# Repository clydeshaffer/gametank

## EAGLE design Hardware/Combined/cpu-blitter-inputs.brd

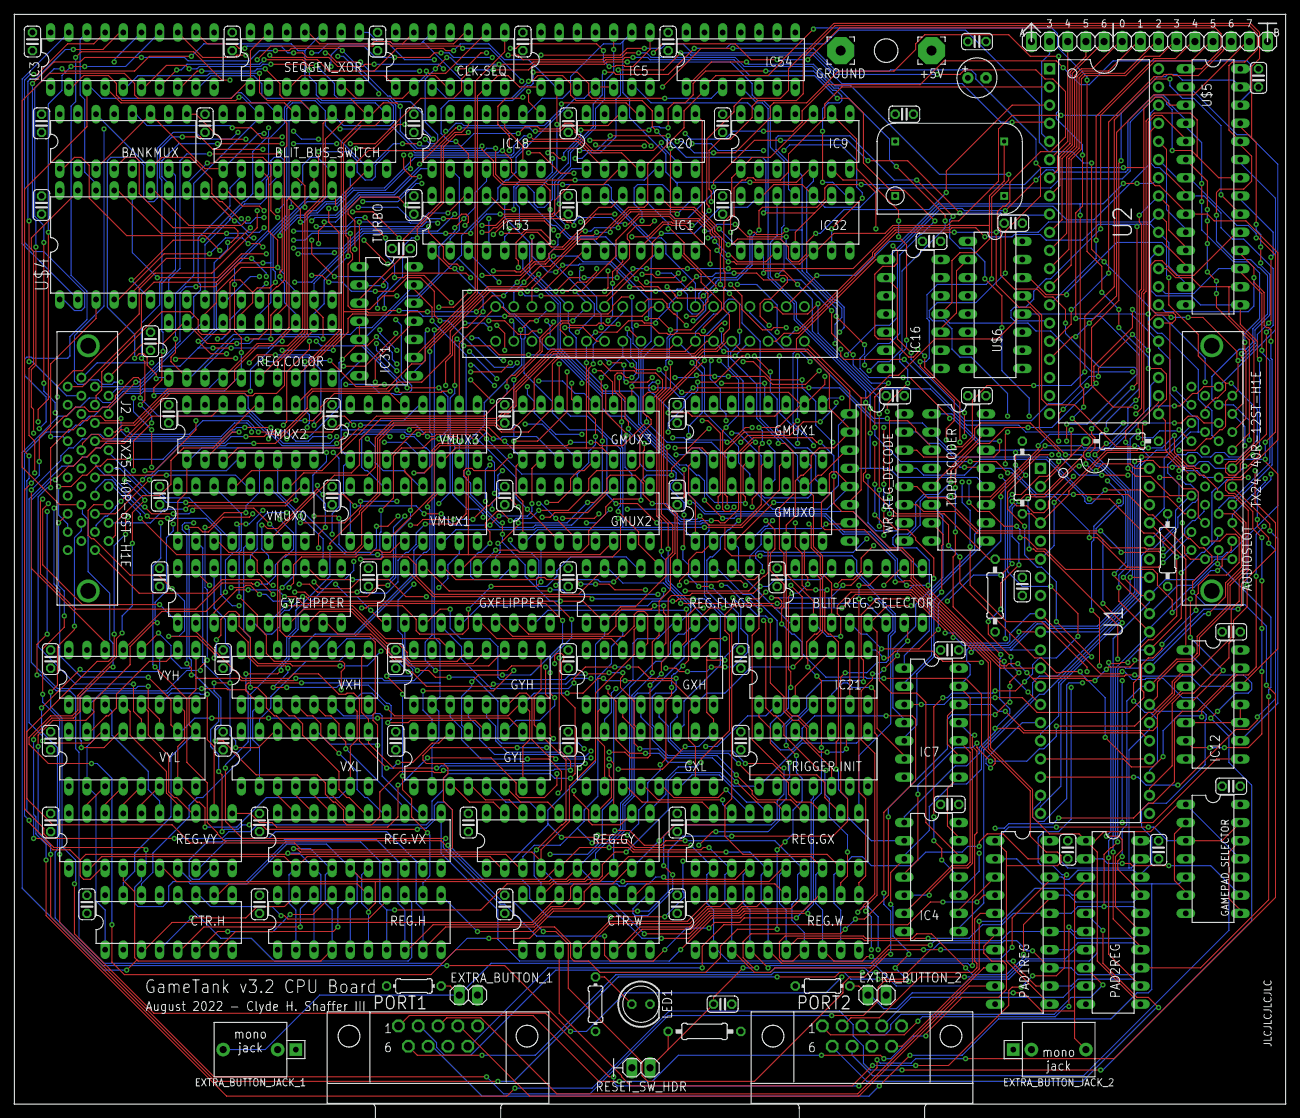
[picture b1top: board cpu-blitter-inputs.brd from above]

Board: 4 copper layers, 177.8 x 152.4 mm, 144 parts (0 on the bottom side), 318 nets.

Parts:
+5V: 3,81/1,4
AUDIOSLOT: TX24-40R-12ST-H1E; CON40_2X20_MU_TX24_JAE
BANKMUX: 74LS257N; DIL16
BLIT_BUS_SWITCH: 74640N; DIL20
BLIT_REG_SELECTOR: 74HC238; DIL16
C1, C2, C3, C4, C5, C6, C7, C8, C9, C10, C11, C12, C13, C14, C15, C16, C17, C18, C19, C20, C21, C22, C23, C24, C25, C26, C27, C28, C29, C30, C31, C32, C33, C34, C35, C36, C38, C39, C40, C41, C42, C43, C44, C45, C46, C57: C025-024X044
C47, C48, C49, C50, C51, C52, C53, C54, C55, C56, C59, C60, C61, C62, C63: 0.1uF; C025-024X044
C58: E2,5-6
CLK.SEQ: 74S08N; DIL14
CTR.H, CTR.W: CD40103; DIL16
EXTRA_BUTTON_1, EXTRA_BUTTON_2: 1X02
EXTRA_BUTTON_JACK_1, EXTRA_BUTTON_JACK_2: MONOJACK
GAMEPAD_SELECTOR: 74LS74N; DIL14
GMUX0, GMUX1, GMUX2, GMUX3: 74LS257N; DIL16
GROUND: 3,81/1,4
GXFLIPPER: 74AHC8541; DIL20
GXH: 74HC163; DIL16
GXL: 74HC163; DIL16
GYFLIPPER: 74AHC8541; DIL20
GYH: 74HC163; DIL16
GYL: 74HC163; DIL16
IC1, IC7, IC12: 74S08N; DIL14
IC3: 74HC573N; DIL20
IC4, IC16, IC53: 7404N; DIL14
IC5, IC21, IC31: 7400N; DIL14
IC9: 74LS74N; DIL14
IC18, IC32: 7432N; DIL14
IC20: 7430N; DIL14
IC54: 74LS07N; DIL14
J2: TX25-40P-6ST-H1E; CON40_2X20_MU_TX25_JAE
LED1: LED5MM
PAD1REG, PAD2REG: 74HC573N; DIL20
PORT1, PORT2: 182-009-MALE
R1, R2, R3, R4, R5: 3.3k; 0207/10
R6, R7: 3.3k; 0204/7
R16: 150; 0204/7
REG.COLOR, REG.FLAGS, REG.GX, REG.GY, REG.H, REG.VX, REG.VY, REG.W: 74HC573N; DIL20
RESET_SW_HDR: 1X02
SEQGEN_XOR: 74LS86N; DIL14
TOPDECODER: 74LS139N; DIL16
TRIGGER.INIT: 74LS74N; DIL14
U1: W65C02SP; DIP-40
U2: VIA; DIP-40
U$2: OSCILLATORMODULEDIL14; CRYSTAL800MIL
U$3: GT_CART3GT_SLOT; SLOT36
U$4: AS6C4008; DIL32
U$5: SRAM_32K; DIL28-3
U$6: 74HC163; DIL16
VIAPORT: 1X14
VMUX0, VMUX1, VMUX2, VMUX3: 74LS257N; DIL16
VXH: 74HC163; DIL16
VXL: 74HC163; DIL16
VYH: 74HC163; DIL16
VYL: 74HC163; DIL16
WR_REG_DECODE: 74HC238; DIL16

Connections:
!AUD_NMI: AUDIOSLOT.16, WR_REG_DECODE.14
!CLK7: IC4.4, IC12.2
!CLK28: IC16.10, U$6.2
!COPYDONE: CTR.H.14, IC9.1, IC9.10
!DIRECT-SELECT: IC18.6, IC18.10, IC32.4, IC32.9
!DMAMODE: GMUX0.1, GMUX1.1, GMUX2.1, GMUX3.1, IC31.6, VMUX0.1, VMUX1.1, VMUX2.1, VMUX3.1
!GAMEPAD1R: GAMEPAD_SELECTOR.3, GAMEPAD_SELECTOR.13, IC53.6, PAD1REG.1, PAD1REG.11
!GAMEPAD2R: GAMEPAD_SELECTOR.1, GAMEPAD_SELECTOR.11, IC53.10, PAD2REG.1, PAD2REG.11
!INIT: CTR.H.15, CTR.W.15, GYH.9, GYL.9, IC1.1, TRIGGER.INIT.1, TRIGGER.INIT.8, VYH.9, VYL.9
!IRQ: AUDIOSLOT.11, IC54.2, R4.2, U1.4, U2.21, U$3.P$21
!IRQ-OUT: IC21.11, IC54.1
!NMI: AUDIOSLOT.10, IC54.4, R3.2, U1.6
!RAMSEL: TOPDECODER.4, U$5.20
!RE2: AUDIOSLOT.13, IC4.8, IC32.10, IC32.13, U$3.P$25, U$5.22
!REGSSEL: IC32.12, TOPDECODER.12, WR_REG_DECODE.4
!RESET: C47.1, R2.2, RESET_SW_HDR.2, U1.40, U2.34, U$3.P$35
!ROWCOMPLETE: CTR.H.3, CTR.W.14, IC1.2, IC53.9
!RUNNING: CTR.W.3, IC9.6
!SEQGEN_HIGH: CLK.SEQ.5, CLK.SEQ.12, SEQGEN_XOR.8
!SEQGEN_LOW: CLK.SEQ.10, CLK.SEQ.13, SEQGEN_XOR.11
!SPI_CS: U2.4, U$3.P$2
!TILEMODE: IC1.5, IC1.13, REG.FLAGS.15
!TRANSEN: IC32.2, REG.FLAGS.12
!TRIGGER: IC31.11, TRIGGER.INIT.4
!VIASEL: TOPDECODER.11, U2.23
!VID_SEL: BLIT_REG_SELECTOR.5, IC7.6, IC18.5
!VOE: J2.13, VMUX3.12
!VWE: J2.12, VMUX1.12
!WAV_SEL: AUDIOSLOT.18, IC7.3
!WE2: AUDIOSLOT.12, BLIT_REG_SELECTOR.4, IC4.12, IC32.5, U$3.P$20, U$5.27
!WRAP_X: IC3.15, IC21.1
!WRAP_Y: IC3.14, IC21.4
!XRELOAD: GXH.9, GXL.9, IC1.3, VXH.9, VXL.9
A0: AUDIOSLOT.32, BLIT_REG_SELECTOR.1, GMUX0.3, IC12.9, IC16.1, U1.9, U2.38, U$3.P$14, U$5.10, VMUX0.3, WR_REG_DECODE.1
A1: AUDIOSLOT.31, BLIT_REG_SELECTOR.2, GMUX0.6, U1.10, U2.37, U$3.P$13, U$5.9, VMUX0.6, WR_REG_DECODE.2
A2: AUDIOSLOT.30, BLIT_REG_SELECTOR.3, GMUX0.10, U1.11, U2.36, U$3.P$12, U$5.8, VMUX0.10, WR_REG_DECODE.3
A3: AUDIOSLOT.29, GMUX0.13, IC12.12, U1.12, U2.35, U$3.P$11, U$5.7, VMUX0.13, WR_REG_DECODE.5
A4: AUDIOSLOT.28, GMUX1.3, U1.13, U$3.P$10, U$5.6, VMUX1.3
A5: AUDIOSLOT.27, GMUX1.6, U1.14, U$3.P$9, U$5.5, VMUX1.6
A6: AUDIOSLOT.26, GMUX1.10, U1.15, U$3.P$8, U$5.4, VMUX1.10
A7: AUDIOSLOT.25, GMUX2.3, U1.16, U$3.P$7, U$5.3, VMUX2.3
A8: AUDIOSLOT.24, GMUX2.6, U1.17, U$3.P$22, U$5.25, VMUX2.6
A9: AUDIOSLOT.23, GMUX2.10, U1.18, U$3.P$23, U$5.24, VMUX2.10
A10: AUDIOSLOT.22, GMUX2.13, U1.19, U$3.P$26, U$5.21, VMUX2.13
A11: AUDIOSLOT.21, GMUX3.3, TOPDECODER.14, U1.20, U$3.P$24, U$5.23, VMUX3.3
A12: AUDIOSLOT.20, GMUX3.6, TOPDECODER.13, U1.22, U$3.P$6, U$5.2, VMUX3.6
A13: AUDIOSLOT.19, GMUX3.10, TOPDECODER.2, U1.23, U$3.P$19, VMUX3.10
A14: TOPDECODER.3, U1.24, U$3.P$33
A15: IC4.1, TOPDECODER.1, U1.25
AUD_LFSR_X: AUDIOSLOT.9, WR_REG_DECODE.11
AUD_RESET: AUDIOSLOT.17, WR_REG_DECODE.15
AUD_SAMP_RATE_SEL: AUDIOSLOT.7, WR_REG_DECODE.9
AUD_SQ2_N: AUDIOSLOT.15, WR_REG_DECODE.13
AUD_SQ2_X: AUDIOSLOT.14, WR_REG_DECODE.12
BE: R5.1, U1.36
CLK3_5: AUDIOSLOT.6, IC12.1, J2.6, SEQGEN_XOR.1, SEQGEN_XOR.13, U1.37, U2.25, U$3.P$18, U$6.12, WR_REG_DECODE.6
CLK7: AUDIOSLOT.5, IC4.3, J2.5, SEQGEN_XOR.4, SEQGEN_XOR.10, U$6.13
CLK14: AUDIOSLOT.4, J2.4, U$6.14
CLK28: AUDIOSLOT.3, IC16.11, J2.3, U$2.P$4
COLORFILL: GMUX3.14, IC5.10, REG.FLAGS.16
D0: AUDIOSLOT.40, BLIT_BUS_SWITCH.18, IC3.2, IC31.13, PAD1REG.12, PAD2REG.12, REG.COLOR.2, REG.FLAGS.2, REG.GX.2, REG.GY.2, REG.H.2, REG.VX.2, REG.VY.2, REG.W.2, U1.33, U2.33, U$3.P$15, U$5.11
D1: AUDIOSLOT.39, BLIT_BUS_SWITCH.17, IC3.3, PAD1REG.13, PAD2REG.13, REG.COLOR.3, REG.FLAGS.3, REG.GX.3, REG.GY.3, REG.H.3, REG.VX.3, REG.VY.3, REG.W.3, U1.32, U2.32, U$3.P$16, U$5.12
D2: AUDIOSLOT.38, BLIT_BUS_SWITCH.16, IC3.4, PAD1REG.14, PAD2REG.14, REG.COLOR.4, REG.FLAGS.4, REG.GX.4, REG.GY.4, REG.H.4, REG.VX.4, REG.VY.4, REG.W.4, U1.31, U2.31, U$3.P$17, U$5.13
D3: AUDIOSLOT.37, BLIT_BUS_SWITCH.15, IC3.5, PAD1REG.15, PAD2REG.15, REG.COLOR.5, REG.FLAGS.5, REG.GX.5, REG.GY.5, REG.H.5, REG.VX.5, REG.VY.5, REG.W.5, U1.30, U2.30, U$3.P$32, U$5.15
D4: AUDIOSLOT.36, BLIT_BUS_SWITCH.14, IC3.6, PAD1REG.16, PAD2REG.16, REG.COLOR.6, REG.FLAGS.6, REG.GX.6, REG.GY.6, REG.H.6, REG.VX.6, REG.VY.6, REG.W.6, U1.29, U2.29, U$3.P$31, U$5.16
D5: AUDIOSLOT.35, BLIT_BUS_SWITCH.13, IC3.7, PAD1REG.17, PAD2REG.17, REG.COLOR.7, REG.FLAGS.7, REG.GX.7, REG.GY.7, REG.H.7, REG.VX.7, REG.VY.7, REG.W.7, U1.28, U2.28, U$3.P$30, U$5.17
D6: AUDIOSLOT.34, BLIT_BUS_SWITCH.12, IC3.8, PAD1REG.18, PAD2REG.18, REG.COLOR.8, REG.FLAGS.8, REG.GX.8, REG.GY.8, REG.H.8, REG.VX.8, REG.VY.8, REG.W.8, U1.27, U2.27, U$3.P$29, U$5.18
D7: AUDIOSLOT.33, BLIT_BUS_SWITCH.11, IC3.9, PAD1REG.19, PAD2REG.19, REG.COLOR.9, REG.FLAGS.9, REG.GX.9, REG.GY.9, REG.H.9, REG.VX.9, REG.VY.9, REG.W.9, U1.26, U2.26, U$3.P$28, U$5.19
DD0: BLIT_BUS_SWITCH.2, IC20.1, J2.40, REG.COLOR.19, U$4.13
DD1: BLIT_BUS_SWITCH.3, IC20.2, J2.39, REG.COLOR.18, U$4.14
DD2: BLIT_BUS_SWITCH.4, IC20.3, J2.38, REG.COLOR.17, U$4.15
DD3: BLIT_BUS_SWITCH.5, IC20.4, J2.37, REG.COLOR.16, U$4.17
DD4: BLIT_BUS_SWITCH.6, IC20.5, J2.36, REG.COLOR.15, U$4.18
DD5: BLIT_BUS_SWITCH.7, IC20.6, J2.35, REG.COLOR.14, U$4.19
DD6: BLIT_BUS_SWITCH.8, IC20.11, J2.34, REG.COLOR.13, U$4.20
DD7: BLIT_BUS_SWITCH.9, IC20.12, J2.33, REG.COLOR.12, U$4.21
DMAMODE: BLIT_REG_SELECTOR.6, IC18.4, IC31.4, IC31.5, REG.FLAGS.19
GA14: GXFLIPPER.12, U$4.3
GA15: GYFLIPPER.12, U$4.31
GA16: IC3.19, U$4.2
GA17: IC3.18, U$4.30
GA18: IC3.17, U$4.1
GND: AUDIOSLOT.2, BANKMUX.8, BANKMUX.15, BLIT_BUS_SWITCH.10, BLIT_REG_SELECTOR.8, C1.2, C2.2, C3.2, C4.2, C5.2, C6.2, C7.2, C8.2, C9.2, C10.2, C11.2, C12.2, C13.2, C14.2, C15.2, C16.2, C17.2, C18.2, C19.2, C20.2, C21.2, C22.2, C23.2, C24.2, C25.2, C26.2, C27.2, C28.2, C29.2, C30.2, C31.2, C32.2, C33.2, C34.2, C35.2, C36.2, C38.2, C39.2, C40.2, C41.2, C42.2, C43.2, C44.2, C45.2, C46.2, C47.2, C48.2, C49.2, C50.2, C51.2, C52.2, C53.2, C54.2, C55.2, C56.2, C57.2, C58.-, C59.2, C60.2, C61.2, C62.2, C63.2, CLK.SEQ.7, CTR.H.8, CTR.H.13, CTR.W.8, CTR.W.13, EXTRA_BUTTON_1.2, EXTRA_BUTTON_2.2, EXTRA_BUTTON_JACK_1.GND, EXTRA_BUTTON_JACK_2.GND, GAMEPAD_SELECTOR.7, GMUX0.8, GMUX0.15, GMUX1.8, GMUX1.15, GMUX2.8, GMUX2.15, GMUX3.8, GMUX3.15, GROUND.1, GXFLIPPER.10, GXFLIPPER.11, GXH.8, GXL.8, GYFLIPPER.10, GYFLIPPER.11, GYH.8, GYL.8, IC1.7, IC3.1, IC3.10, IC4.7, IC5.7, IC7.7, IC9.2, IC9.3, IC9.7, IC9.11, IC9.12, IC12.7, IC16.7, IC18.7, IC20.7, IC21.7, IC31.7, IC32.7, IC53.7, IC54.7, J2.2, LED1.K, PAD1REG.10, PAD2REG.10, PORT1.8, PORT2.8, REG.COLOR.10, REG.FLAGS.1, REG.FLAGS.10, REG.GX.1, REG.GX.10, REG.GY.1, REG.GY.10, REG.H.1, REG.H.10, REG.VX.1, REG.VX.10, REG.VY.1, REG.VY.10, REG.W.1, REG.W.10, RESET_SW_HDR.1, SEQGEN_XOR.2, SEQGEN_XOR.5, SEQGEN_XOR.7, TOPDECODER.8, TRIGGER.INIT.2, TRIGGER.INIT.3, TRIGGER.INIT.7, U1.21, U2.1, U$2.P$2, U$3.P$36, U$4.16, U$4.22, U$5.14, U$6.3, U$6.4, U$6.5, U$6.6, U$6.8, VIAPORT.14, VMUX0.8, VMUX0.15, VMUX1.8, VMUX1.15, VMUX2.8, VMUX2.15, VMUX3.8, VMUX3.15, VXH.8, VXL.8, VYH.8, VYL.8, WR_REG_DECODE.8
GRAM_PAGE_SEL: IC3.11, WR_REG_DECODE.10
GX-CARRY: GXH.10, IC1.6
GX-CARRY?: GXL.15, IC1.4
GY-CARRY: GYH.10, IC1.11
GY-CARRY?: GYL.15, IC1.12
IRQ: IC9.9, IC21.12
IRQ-ENABLE: IC21.13, REG.FLAGS.13
unnamed: GMUX0.4, U$4.12
unnamed: GMUX0.7, U$4.11
unnamed: GMUX0.9, U$4.10
unnamed: GMUX0.12, U$4.9
unnamed: GMUX1.4, U$4.8
unnamed: GMUX1.7, U$4.7
unnamed: GMUX1.9, U$4.6
unnamed: GMUX2.4, U$4.5
unnamed: GMUX2.7, U$4.27
unnamed: GMUX2.9, U$4.26
unnamed: GMUX2.12, U$4.23
unnamed: GMUX3.4, U$4.25
unnamed: GMUX3.7, U$4.4
unnamed: GMUX3.9, U$4.28
unnamed: IC18.11, VMUX1.14
unnamed: IC31.1, IC32.3
unnamed: GMUX1.12, U$4.29
unnamed: GMUX3.12, U$4.24
unnamed: GYL.3, REG.GY.19
unnamed: GYL.4, REG.GY.18
unnamed: GYL.5, REG.GY.17
unnamed: GYL.6, REG.GY.16
unnamed: GXH.3, REG.GX.15
unnamed: GXH.4, REG.GX.14
unnamed: GXH.5, REG.GX.13
unnamed: GYH.3, REG.GY.15
unnamed: GXL.3, REG.GX.19
unnamed: GXL.4, REG.GX.18
unnamed: GXL.5, REG.GX.17
unnamed: GXL.6, REG.GX.16
unnamed: GYH.4, REG.GY.14
unnamed: GYH.5, REG.GY.13
unnamed: IC18.3, IC54.3
unnamed: IC12.8, IC53.11
unnamed: REG.VY.15, VYH.3
unnamed: REG.VY.14, VYH.4
unnamed: REG.VY.13, VYH.5
unnamed: IC7.5, TOPDECODER.7
unnamed: IC18.2, IC53.2
unnamed: IC7.4, TOPDECODER.6
unnamed: IC1.8, IC31.2
unnamed: TOPDECODER.5, TOPDECODER.15
unnamed: IC18.13, IC21.8
unnamed: IC5.8, REG.COLOR.1
unnamed: GXFLIPPER.5, GXL.11
unnamed: GXFLIPPER.4, GXL.12
unnamed: IC21.6, IC21.9
unnamed: IC21.3, IC21.10
unnamed: IC18.12, IC31.3
unnamed: GXFLIPPER.3, GXL.13
unnamed: GXFLIPPER.2, GXL.14
unnamed: GXFLIPPER.6, GXH.14
unnamed: BANKMUX.4, VMUX1.13
unnamed: CTR.H.4, REG.H.19
unnamed: CTR.H.5, REG.H.18
unnamed: CTR.H.6, REG.H.17
unnamed: CTR.H.7, REG.H.16
unnamed: CTR.H.10, REG.H.15
unnamed: CTR.H.11, REG.H.14
unnamed: CTR.H.12, REG.H.13
unnamed: IC31.10, TRIGGER.INIT.9
unnamed: CTR.W.4, REG.W.19
unnamed: CTR.W.5, REG.W.18
unnamed: CTR.W.6, REG.W.17
unnamed: CTR.W.7, REG.W.16
unnamed: CTR.W.10, REG.W.15
unnamed: CTR.W.11, REG.W.14
unnamed: CTR.W.12, REG.W.13
unnamed: IC20.8, IC32.1
unnamed: BANKMUX.7, VMUX3.13
unnamed: GXFLIPPER.7, GXH.13
unnamed: BANKMUX.9, GMUX1.13
unnamed: BANKMUX.12, GMUX3.13
unnamed: BLIT_REG_SELECTOR.15, REG.VX.11
unnamed: GXFLIPPER.8, GXH.12
unnamed: GYFLIPPER.2, GYL.14
unnamed: GYFLIPPER.3, GYL.13
unnamed: GYFLIPPER.4, GYL.12
unnamed: GYFLIPPER.5, GYL.11
unnamed: GYFLIPPER.6, GYH.14
unnamed: GYFLIPPER.7, GYH.13
unnamed: GYFLIPPER.8, GYH.12
unnamed: GYFLIPPER.1, IC53.4
unnamed: GXFLIPPER.1, IC53.12
unnamed: IC9.4, IC31.8, TRIGGER.INIT.13
unnamed: REG.VX.12, VXH.6
unnamed: REG.VY.12, VYH.6
unnamed: GXFLIPPER.9, GXH.11
unnamed: IC7.2, TOPDECODER.9
unnamed: CTR.W.9, IC5.3
unnamed: IC5.6, IC9.13
unnamed: GYFLIPPER.9, GYH.11
unnamed: IC7.1, TOPDECODER.10
unnamed: BLIT_REG_SELECTOR.14, REG.VY.11
unnamed: BLIT_REG_SELECTOR.13, REG.GX.11
unnamed: BLIT_REG_SELECTOR.12, REG.GY.11
unnamed: IC4.13, IC7.8
unnamed: IC4.9, IC7.11
unnamed: IC7.9, IC7.12, IC12.3
unnamed: U2.10, VIAPORT.6
unnamed: U2.11, VIAPORT.7
unnamed: U2.14, VIAPORT.10
unnamed: U2.15, VIAPORT.11
unnamed: U2.16, VIAPORT.12
unnamed: BLIT_REG_SELECTOR.11, REG.W.11
unnamed: U2.17, VIAPORT.13
unnamed: U2.12, VIAPORT.8
unnamed: BLIT_REG_SELECTOR.10, REG.H.11
unnamed: U2.13, VIAPORT.9
unnamed: REG.VY.19, VYL.3
unnamed: REG.VY.18, VYL.4
unnamed: REG.VY.17, VYL.5
unnamed: REG.VY.16, VYL.6
unnamed: REG.VX.15, VXH.3
unnamed: REG.VX.14, VXH.4
unnamed: REG.VX.13, VXH.5
unnamed: U2.5, VIAPORT.2
unnamed: REG.VX.19, VXL.3
unnamed: REG.VX.18, VXL.4
unnamed: REG.VX.17, VXL.5
unnamed: REG.VX.16, VXL.6
unnamed: BLIT_REG_SELECTOR.7, REG.COLOR.11
unnamed: U2.6, VIAPORT.3
unnamed: U2.7, VIAPORT.4
unnamed: U2.8, VIAPORT.5
unnamed: IC12.6, IC53.5
unnamed: LED1.A, R16.2
unnamed: GAMEPAD_SELECTOR.8, GAMEPAD_SELECTOR.12
unnamed: GAMEPAD_SELECTOR.9, PAD2REG.2, PORT2.7
unnamed: GAMEPAD_SELECTOR.2, GAMEPAD_SELECTOR.6
unnamed: GAMEPAD_SELECTOR.5, PAD1REG.2, PORT1.7
unnamed: PAD1REG.4, PORT1.9
unnamed: PAD1REG.5, PORT1.6
unnamed: PAD1REG.6, PORT1.1
unnamed: PAD1REG.7, PORT1.2
unnamed: PAD1REG.8, PORT1.3
unnamed: PAD1REG.9, PORT1.4
unnamed: PAD2REG.6, PORT2.1
unnamed: PAD2REG.7, PORT2.2
unnamed: PAD2REG.8, PORT2.3
unnamed: PAD2REG.9, PORT2.4
unnamed: PAD2REG.4, PORT2.9
unnamed: PAD2REG.5, PORT2.6
unnamed: EXTRA_BUTTON_1.1, EXTRA_BUTTON_JACK_1.WAV, PAD1REG.3, R7.2
unnamed: EXTRA_BUTTON_2.1, EXTRA_BUTTON_JACK_2.WAV, PAD2REG.3, R6.2
unnamed: IC4.10, IC12.13
unnamed: GXH.6, REG.GX.12
unnamed: GYH.6, REG.GY.12
unnamed: IC4.11, IC32.11
unnamed: IC12.5, IC12.10, IC12.11
unnamed: IC12.4, IC16.2
unnamed: VMUX0.5, VXL.13
unnamed: VMUX0.11, VXL.12
unnamed: VMUX0.14, VXL.11
unnamed: VMUX1.2, VXH.14
unnamed: VMUX1.5, VXH.13
unnamed: VMUX1.11, VXH.12
unnamed: VMUX2.5, VYL.13
unnamed: VMUX2.11, VYL.12
unnamed: VMUX2.14, VYL.11
unnamed: VMUX3.2, VYH.14
unnamed: VMUX3.5, VYH.13
unnamed: VMUX3.11, VYH.12
unnamed: GMUX0.2, GXFLIPPER.19
unnamed: GMUX0.5, GXFLIPPER.18
unnamed: GMUX0.11, GXFLIPPER.17
unnamed: GMUX0.14, GXFLIPPER.16
unnamed: GMUX1.2, GXFLIPPER.15
unnamed: GMUX1.5, GXFLIPPER.14
unnamed: GMUX1.11, GXFLIPPER.13
unnamed: GMUX2.2, GYFLIPPER.19
unnamed: GMUX2.5, GYFLIPPER.18
unnamed: GMUX2.11, GYFLIPPER.17
unnamed: GMUX2.14, GYFLIPPER.16
unnamed: GMUX3.2, GYFLIPPER.15
unnamed: GMUX3.5, GYFLIPPER.14
unnamed: GMUX3.11, GYFLIPPER.13
unnamed: BLIT_BUS_SWITCH.19, IC18.8
OFFSCR_X: IC21.2, VXH.11
OFFSCR_Y: IC21.5, VYH.11
P0: CLK.SEQ.11, CTR.W.1
P1: CLK.SEQ.8, CTR.H.1, GXH.2, GXL.2, GYH.2, GYL.2, VXH.2, VXL.2, VYH.2, VYL.2
P2: CLK.SEQ.6, IC5.1, IC31.9
P3: CLK.SEQ.3, IC1.10, TRIGGER.INIT.11
R/!W!: IC4.5, IC7.13, U1.34, U2.22
RAM_PG_0: IC3.13, U$5.26
RAM_PG_1: IC3.12, U$5.1
READY: R1.1, U1.2, U$3.P$34
ROWCOMPLETE: GYL.10, IC5.2, IC53.8, VYL.10
RUNNING: GXH.7, GXL.7, GYH.7, GYL.7, IC1.9, IC5.9, IC9.5, IC18.9, VXH.7, VXL.7, VYH.7, VYL.7
SEQGEN_HIGH: CLK.SEQ.2, CLK.SEQ.9, SEQGEN_XOR.6
SEQGEN_LOW: CLK.SEQ.1, CLK.SEQ.4, SEQGEN_XOR.3
SPI_CLK: U2.2, U$3.P$5
SPI_MISO: U2.9, U$3.P$3
SPI_MOSI: U2.3, U$3.P$4
TRIGGER-FLAG: TRIGGER.INIT.5, TRIGGER.INIT.12
TRIGGER-SELECT: BLIT_REG_SELECTOR.9, IC5.4, IC5.5, IC31.12
V/_G: BANKMUX.1, REG.FLAGS.14
VA0: J2.32, VMUX0.4
VA1: J2.31, VMUX0.7
VA2: J2.30, VMUX0.9
VA3: J2.29, VMUX0.12
VA4: J2.28, VMUX1.4
VA5: J2.27, VMUX1.7
VA6: J2.26, VMUX1.9
VA7: J2.25, VMUX2.4
VA8: J2.24, VMUX2.7
VA9: J2.23, VMUX2.9
VA10: J2.22, VMUX2.12
VA11: J2.21, VMUX3.4
VA12: J2.20, VMUX3.7
VA13: J2.19, VMUX3.9
VCC: +5V.1, AUDIOSLOT.1, BANKMUX.2, BANKMUX.5, BANKMUX.10, BANKMUX.13, BANKMUX.16, BLIT_BUS_SWITCH.20, BLIT_REG_SELECTOR.16, C1.1, C2.1, C3.1, C4.1, C5.1, C6.1, C7.1, C8.1, C9.1, C10.1, C11.1, C12.1, C13.1, C14.1, C15.1, C16.1, C17.1, C18.1, C19.1, C20.1, C21.1, C22.1, C23.1, C24.1, C25.1, C26.1, C27.1, C28.1, C29.1, C30.1, C31.1, C32.1, C33.1, C34.1, C35.1, C36.1, C38.1, C39.1, C40.1, C41.1, C42.1, C43.1, C44.1, C45.1, C46.1, C48.1, C49.1, C50.1, C51.1, C52.1, C53.1, C54.1, C55.1, C56.1, C57.1, C58.+, C59.1, C60.1, C61.1, C62.1, C63.1, CLK.SEQ.14, CTR.H.2, CTR.H.9, CTR.H.16, CTR.W.2, CTR.W.16, GAMEPAD_SELECTOR.4, GAMEPAD_SELECTOR.10, GAMEPAD_SELECTOR.14, GMUX0.16, GMUX1.14, GMUX1.16, GMUX2.16, GMUX3.16, GXFLIPPER.20, GXH.1, GXH.16, GXL.1, GXL.10, GXL.16, GYFLIPPER.20, GYH.1, GYH.16, GYL.1, GYL.16, IC1.14, IC3.20, IC4.14, IC5.14, IC7.14, IC9.14, IC12.14, IC16.14, IC18.14, IC20.14, IC21.14, IC31.14, IC32.14, IC53.14, IC54.14, J2.1, PAD1REG.20, PAD2REG.20, PORT1.5, PORT2.5, R1.2, R2.1, R3.1, R4.1, R5.2, R6.1, R7.1, R16.1, REG.COLOR.20, REG.FLAGS.20, REG.GX.20, REG.GY.20, REG.H.20, REG.VX.20, REG.VY.20, REG.W.20, SEQGEN_XOR.9, SEQGEN_XOR.12, SEQGEN_XOR.14, TOPDECODER.16, TRIGGER.INIT.10, TRIGGER.INIT.14, U1.8, U1.38, U2.20, U2.24, U$2.P$3, U$3.P$1, U$4.32, U$5.28, U$6.1, U$6.7, U$6.9, U$6.10, U$6.16, VIAPORT.1, VMUX0.16, VMUX1.16, VMUX2.16, VMUX3.14, VMUX3.16, VXH.1, VXH.16, VXL.1, VXL.10, VXL.16, VYH.1, VYH.16, VYL.1, VYL.16, WR_REG_DECODE.16
VG_OE: BANKMUX.6, BANKMUX.14, IC32.8
VG_WE: BANKMUX.3, BANKMUX.11, BLIT_BUS_SWITCH.1, IC32.6
VIDFLAGS: REG.FLAGS.11, WR_REG_DECODE.7
VID_OUT_PAGE: J2.17, REG.FLAGS.18
VNMI: IC18.1, J2.10
VNMI_ENABLE: IC53.1, REG.FLAGS.17
VRAMBANK: IC3.16, J2.18
VX-CARRY: VXH.10, VXL.15
VY-CARRY: VYH.10, VYL.15
W/!R!: IC4.6, IC7.10
XDIR: IC53.13, REG.W.12
XODD: VMUX0.2, VXL.14
YDIR: IC53.3, REG.H.12
YODD: VMUX2.2, VYL.14
_CARTSEL: IC4.2, U$3.P$27

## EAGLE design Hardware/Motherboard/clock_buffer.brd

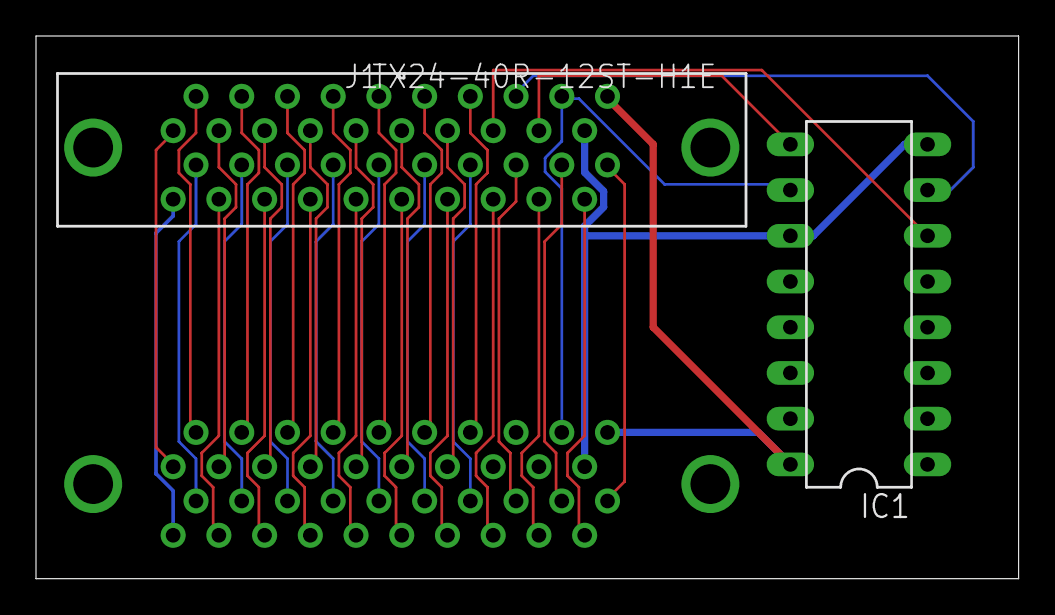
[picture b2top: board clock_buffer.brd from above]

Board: 2 copper layers, 54.6 x 30.1 mm, 3 parts (1 on the bottom side), 40 nets.

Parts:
IC1: 4040N; DIL16
J1: TX24-40R-12ST-H1E; CON40_2X20_MU_TX24_JAE
J2: TX25-40P-6ST-H1E; CON40_2X20_MU_TX25_JAE

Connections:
GND: IC1.8, IC1.11, J1.2, J2.2
unnamed: IC1.9, J1.4
unnamed: IC1.7, J1.5
unnamed: IC1.6, J1.6
unnamed: IC1.10, J1.3, J2.3
unnamed: J1.7, J2.7
unnamed: J1.8, J2.8
unnamed: J1.9, J2.9
unnamed: J1.10, J2.10
unnamed: J1.11, J2.11
unnamed: J1.12, J2.12
unnamed: J1.13, J2.13
unnamed: J1.14, J2.14
unnamed: J1.15, J2.15
unnamed: J1.16, J2.16
unnamed: J1.17, J2.17
unnamed: J1.18, J2.18
unnamed: J1.19, J2.19
unnamed: J1.20, J2.20
unnamed: J1.21, J2.21
unnamed: J1.22, J2.22
unnamed: J1.23, J2.23
unnamed: J1.24, J2.24
unnamed: J1.25, J2.25
unnamed: J1.26, J2.26
unnamed: J1.27, J2.27
unnamed: J1.28, J2.28
unnamed: J1.29, J2.29
unnamed: J1.30, J2.30
unnamed: J1.31, J2.31
unnamed: J1.32, J2.32
unnamed: J1.33, J2.33
unnamed: J1.34, J2.34
unnamed: J1.35, J2.35
unnamed: J1.36, J2.36
unnamed: J1.37, J2.37
unnamed: J1.38, J2.38
unnamed: J1.39, J2.39
unnamed: J1.40, J2.40
VCC: IC1.16, J1.1, J2.1

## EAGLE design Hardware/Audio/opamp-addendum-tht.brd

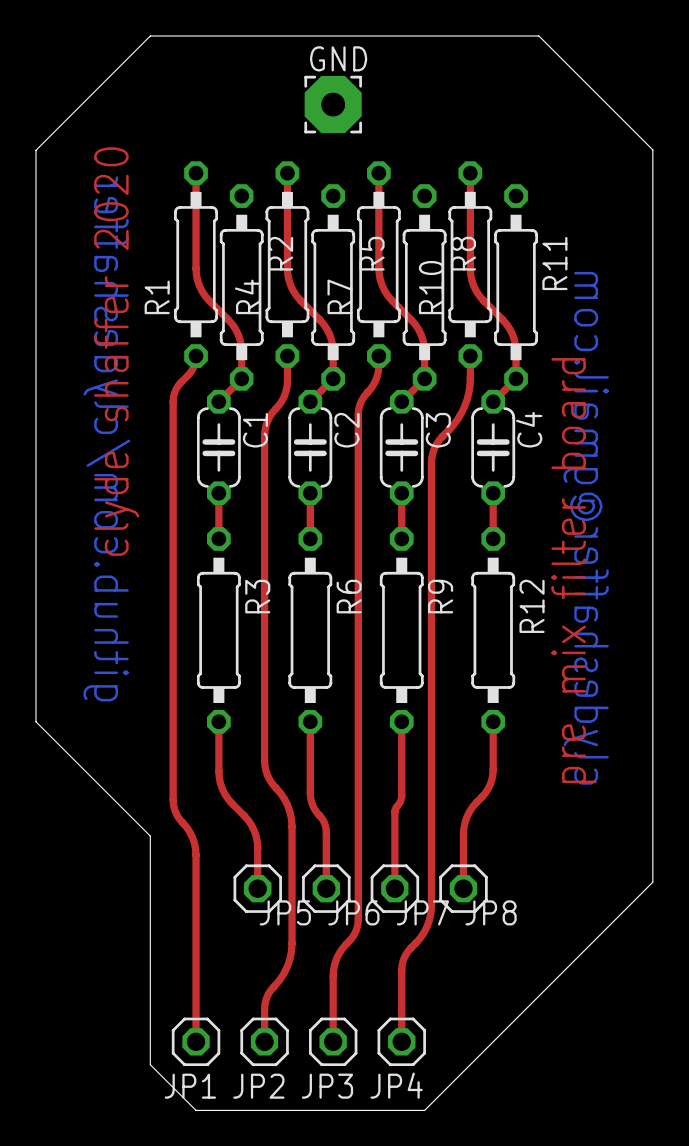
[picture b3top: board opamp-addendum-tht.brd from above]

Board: 2 copper layers, 34.3 x 59.7 mm, 25 parts (0 on the bottom side), 17 nets.

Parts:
C1, C2, C3, C4: 104; C050-024X044
GND: WIREPAD3,17/1,3; 3,17/1,3
JP1, JP2, JP3, JP4, JP5, JP6, JP7, JP8: 1X01
R1, R4, R7, R11: 10k; 0207/10
R2, R5, R8, R10: 1k; 0207/10
R3, R6, R9, R12: 3k3; 0207/10

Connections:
CH1: JP1.1, R1.1
CH2: JP2.1, R4.1
CH3: JP3.1, R7.1
CH4: JP4.1, R10.1
GND: GND.1, R2.1, R5.1, R8.1, R11.1
unnamed: C1.1, R1.2, R2.2
unnamed: C2.1, R4.2, R5.2
unnamed: C3.1, R7.2, R8.2
unnamed: C4.1, R10.2, R11.2
unnamed: C1.2, R3.1
unnamed: C2.2, R6.1
unnamed: C3.2, R9.1
unnamed: C4.2, R12.1
unnamed: JP8.1, R12.2
unnamed: JP5.1, R3.2
unnamed: JP6.1, R6.2
unnamed: JP7.1, R9.2

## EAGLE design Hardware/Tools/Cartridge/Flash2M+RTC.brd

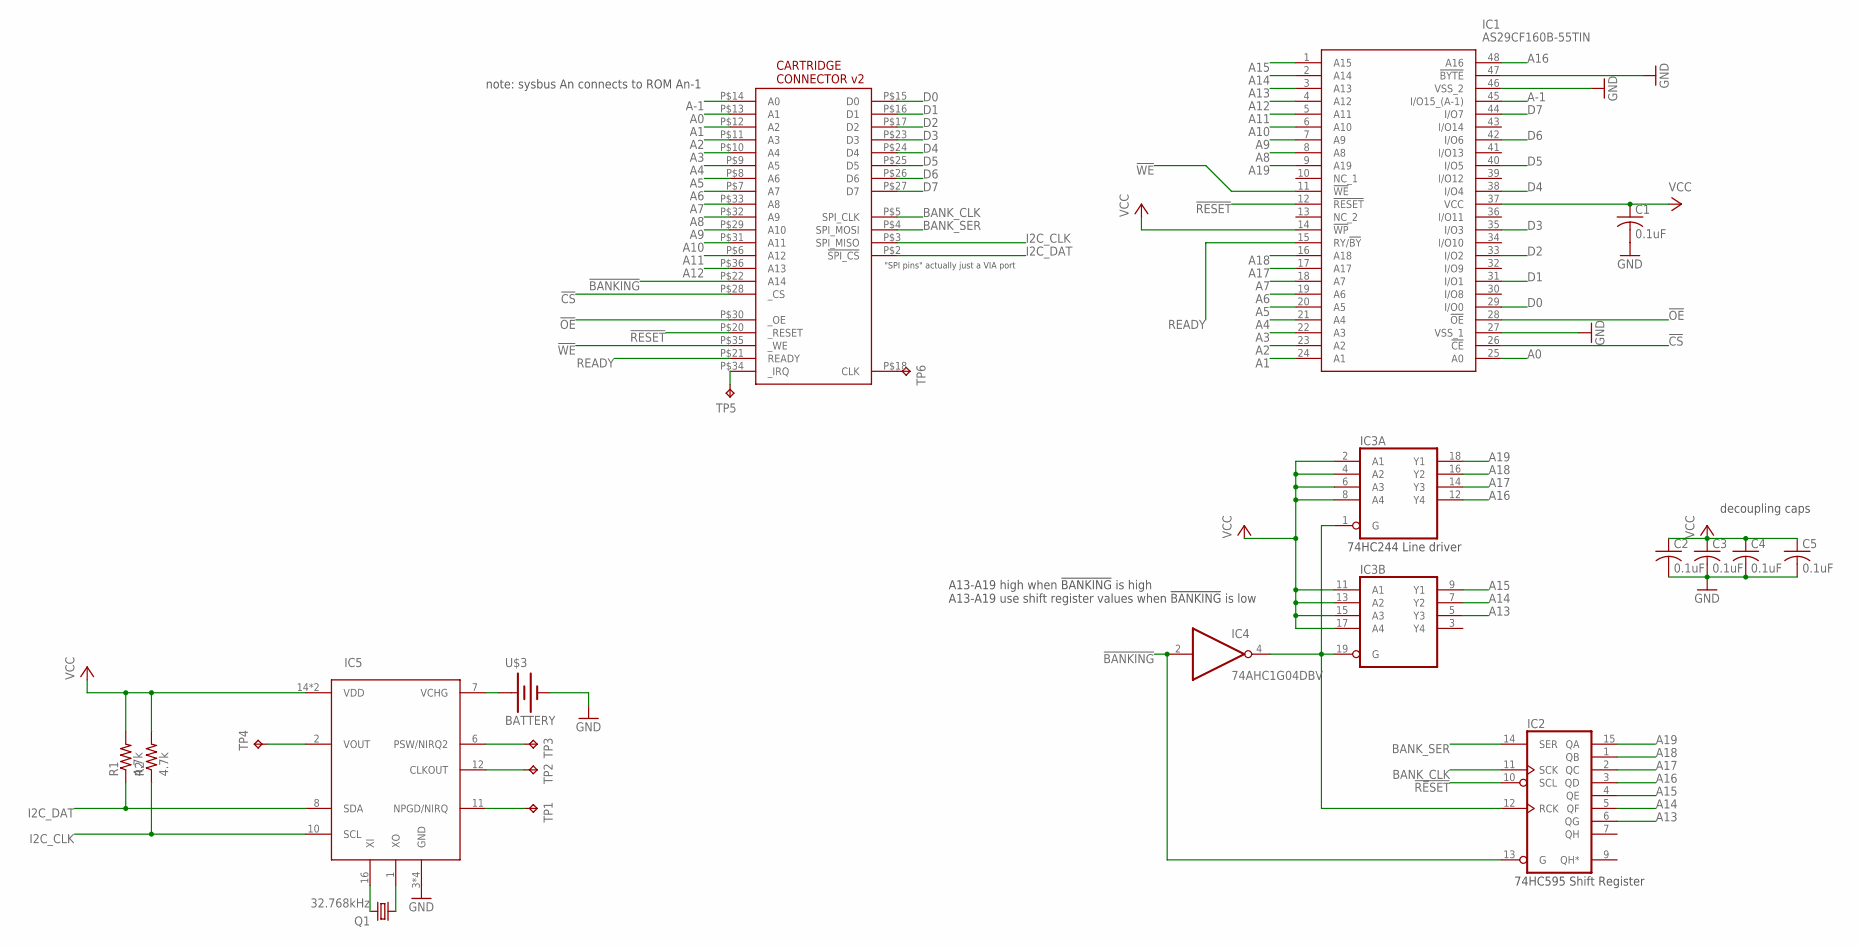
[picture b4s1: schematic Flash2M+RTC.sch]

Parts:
C1, C2, C3, C4, C5: 0.1uF; C0805
IC1: AS29CF160B-55TIN; SOP50P2000X120-48N
IC2: 74LS595D; SO16
IC3: 74LS244DW; SO20W
IC4: 74AHC1G04DBV; SOT23-5
IC5: PMRTC-CBC921; QFN16
Q1: 32.768kHz; TC38H
R1, R2: 4.7k; R0805
TP1, TP2, TP3, TP4, TP5, TP6: TPB1,27; B1,27
U$1: GT_CART3GT_CARD; CARD36
U$3: BATTERY; BATTHOLDER-6.8

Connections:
!BANKING: IC2.13 (G), IC4.2 (I), U$1.P$22 (A14)
!CS: IC1.26 (!CE), U$1.P$28 (_CS)
!OE: IC1.28 (!OE), U$1.P$30 (_OE)
!RESET: IC1.12 (!RESET), IC2.10 (SCL), U$1.P$20 (_RESET)
!WE: IC1.11 (!WE), U$1.P$35 (_WE)
A0: IC1.25 (A0), U$1.P$13 (A1)
A1: IC1.24 (A1), U$1.P$12 (A2)
A2: IC1.23 (A2), U$1.P$11 (A3)
A3: IC1.22 (A3), U$1.P$10 (A4)
A4: IC1.21 (A4), U$1.P$9 (A5)
A5: IC1.20 (A5), U$1.P$8 (A6)
A6: IC1.19 (A6), U$1.P$7 (A7)
A7: IC1.18 (A7), U$1.P$33 (A8)
A8: IC1.8 (A8), U$1.P$32 (A9)
A9: IC1.7 (A9), U$1.P$29 (A10)
A10: IC1.6 (A10), U$1.P$31 (A11)
A11: IC1.5 (A11), U$1.P$6 (A12)
A12: IC1.4 (A12), U$1.P$36 (A13)
A13: IC1.3 (A13), IC2.6 (QG), IC3.5 (Y3)
A14: IC1.2 (A14), IC2.5 (QF), IC3.7 (Y2)
A15: IC1.1 (A15), IC2.4 (QE), IC3.9 (Y1)
A16: IC1.48 (A16), IC2.3 (QD), IC3.12 (Y4)
A17: IC1.17 (A17), IC2.2 (QC), IC3.14 (Y3)
A18: IC1.16 (A18), IC2.1 (QB), IC3.16 (Y2)
A19: IC1.9 (A19), IC2.15 (QA), IC3.18 (Y1)
A-1: IC1.45 (I/O15_(A-1)), U$1.P$14 (A0)
BANK_CLK: IC2.11 (SCK), U$1.P$5 (SPI_CLK)
BANK_SER: IC2.14 (SER), U$1.P$4 (SPI_MOSI)
D0: IC1.29 (I/O0), U$1.P$15 (D0)
D1: IC1.31 (I/O1), U$1.P$16 (D1)
D2: IC1.33 (I/O2), U$1.P$17 (D2)
D3: IC1.35 (I/O3), U$1.P$23 (D3)
D4: IC1.38 (I/O4), U$1.P$24 (D4)
D5: IC1.40 (I/O5), U$1.P$25 (D5)
D6: IC1.42 (I/O6), U$1.P$26 (D6)
D7: IC1.44 (I/O7), U$1.P$27 (D7)
GND: C1.2, C2.2, C3.2, C4.2, C5.2, IC1.27 (VSS_1), IC1.46 (VSS_2), IC1.47 (!BYTE), IC2.8 (GND), IC3.10 (GND), IC4.3 (GND), IC5.3 (GND), IC5.4 (GND), IC5.5 (GND), IC5.EXP (GND), U$1.P$19 (GND), U$3.V_3 (-)
I2C_CLK: IC5.10 (SCL), R2.1, U$1.P$3 (SPI_MISO)
I2C_DAT: IC5.8 (SDA), R1.1, U$1.P$2 (!SPI_CS)
unnamed: IC2.12 (RCK), IC3.1 (G), IC3.19 (G), IC4.4 (O)
unnamed: IC5.16 (XI), Q1.2
unnamed: IC5.6 (PSW/NIRQ2), TP3.TP
unnamed: IC5.1 (XO), Q1.1
unnamed: IC5.7 (VCHG), U$3.V_1 (+), U$3.V_2 (+)
unnamed: IC5.12 (CLKOUT), TP2.TP
unnamed: IC5.11 (NPGD/NIRQ), TP1.TP
unnamed: IC5.2 (VOUT), TP4.TP
unnamed: TP5.TP, U$1.P$34 (_IRQ)
unnamed: TP6.TP, U$1.P$18 (CLK)
READY: IC1.15 (RY/!BY), U$1.P$21 (READY)
VCC: C1.1, C2.1, C3.1, C4.1, C5.1, IC1.14 (!WP), IC1.37 (VCC), IC2.16 (VCC), IC3.2 (A1), IC3.4 (A2), IC3.6 (A3), IC3.8 (A4), IC3.11 (A1), IC3.13 (A2), IC3.15 (A3), IC3.17 (A4), IC3.20 (VCC), IC4.5 (VCC), IC5.14 (VDD), IC5.15 (VDD), R1.2, R2.2, U$1.P$1 (VCC)

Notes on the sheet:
note: sysbus An connects to ROM An-1
74HC244 Line driver
74HC595 Shift Register
A13-A19 high when !BANKING! is high A13-A19 use shift register values when !BANKING! is low
"SPI pins" actually just a VIA port
decoupling caps

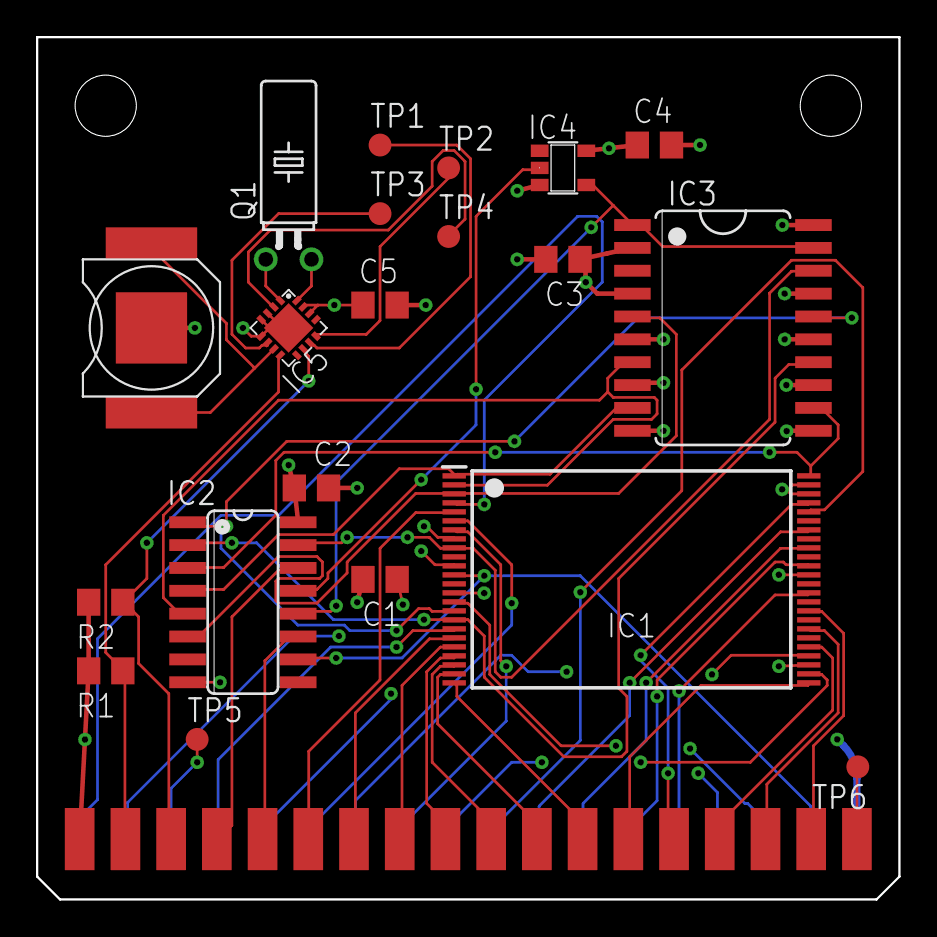
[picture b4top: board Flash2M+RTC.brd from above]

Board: 4 copper layers, 47.9 x 47.9 mm, 21 parts (0 on the bottom side), 51 nets.

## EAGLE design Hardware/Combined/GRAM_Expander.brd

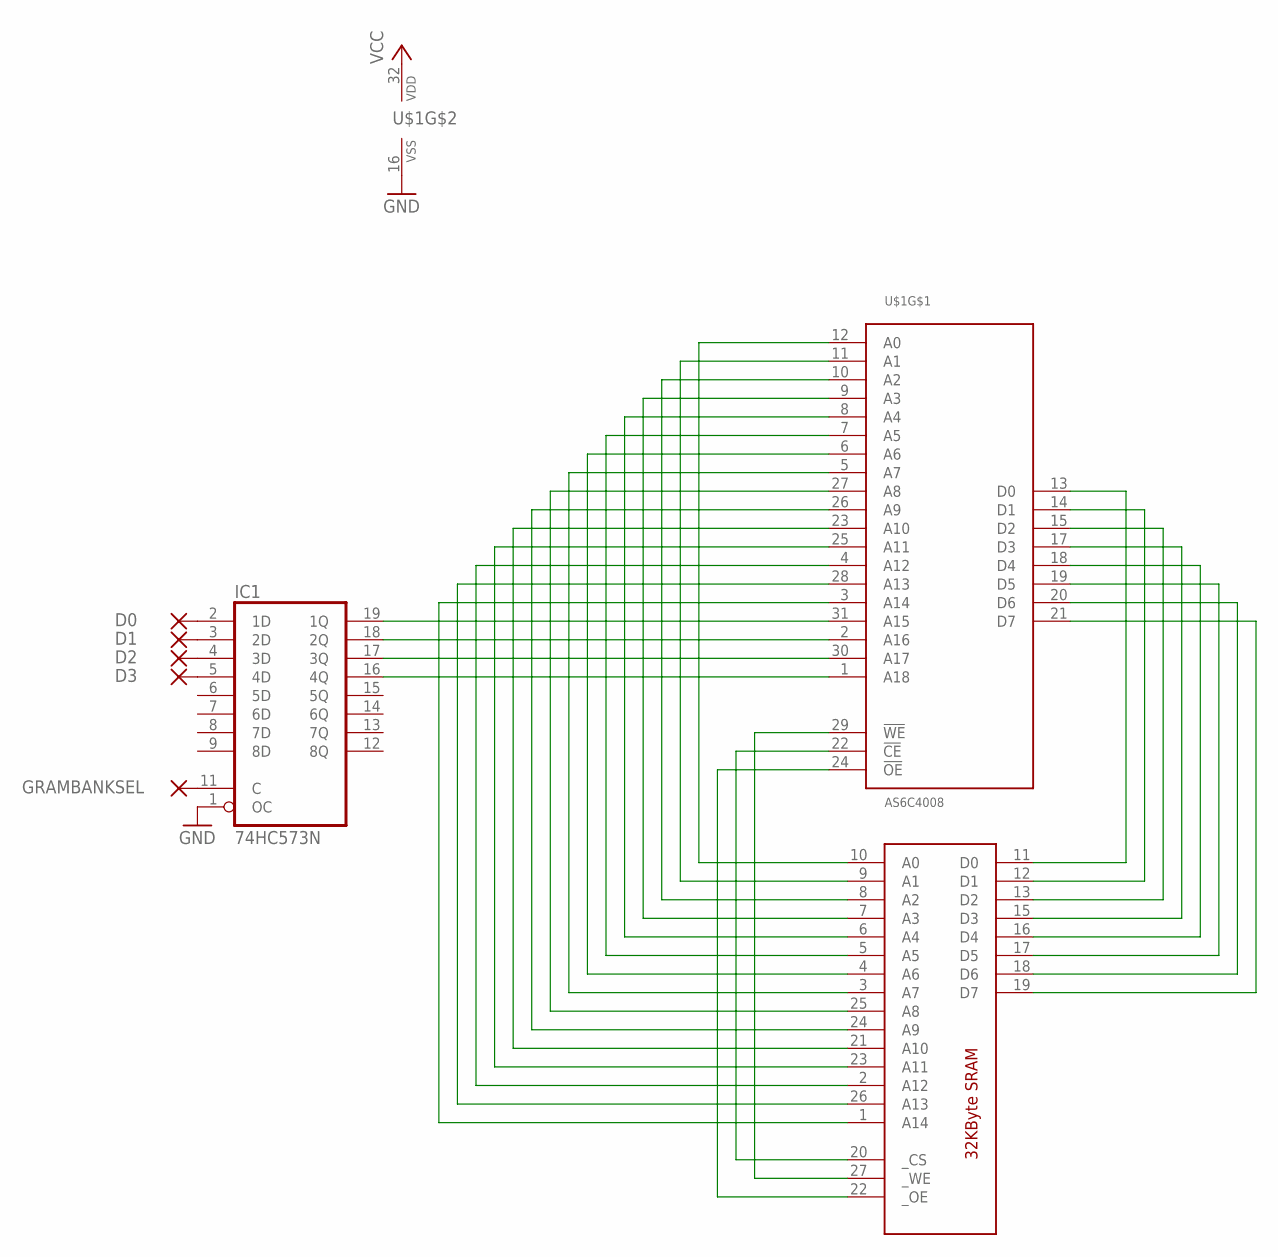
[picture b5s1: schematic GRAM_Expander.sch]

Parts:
D0, D1, D2, D3: 1,6/0,8
GRAMBANKSEL: 1,6/0,8
IC1: 74HC573N; DIL20
U$1: AS6C4008; DIL32
U$2: SRAM_32K; DIL28-3

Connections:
GND: IC1.1 (OC), IC1.10 (GND), U$1.16 (VSS), U$2.14 (GND)
unnamed: U$1.13 (D0), U$2.11 (D0)
unnamed: U$1.14 (D1), U$2.12 (D1)
unnamed: U$1.15 (D2), U$2.13 (D2)
unnamed: U$1.17 (D3), U$2.15 (D3)
unnamed: U$1.18 (D4), U$2.16 (D4)
unnamed: U$1.19 (D5), U$2.17 (D5)
unnamed: U$1.20 (D6), U$2.18 (D6)
unnamed: U$1.21 (D7), U$2.19 (D7)
unnamed: U$1.12 (A0), U$2.10 (A0)
unnamed: U$1.11 (A1), U$2.9 (A1)
unnamed: U$1.10 (A2), U$2.8 (A2)
unnamed: U$1.9 (A3), U$2.7 (A3)
unnamed: U$1.8 (A4), U$2.6 (A4)
unnamed: U$1.7 (A5), U$2.5 (A5)
unnamed: U$1.6 (A6), U$2.4 (A6)
unnamed: U$1.5 (A7), U$2.3 (A7)
unnamed: U$1.27 (A8), U$2.25 (A8)
unnamed: U$1.26 (A9), U$2.24 (A9)
unnamed: U$1.23 (A10), U$2.21 (A10)
unnamed: U$1.25 (A11), U$2.23 (A11)
unnamed: U$1.4 (A12), U$2.2 (A12)
unnamed: U$1.28 (A13), U$2.26 (A13)
unnamed: U$1.3 (A14), U$2.1 (A14)
unnamed: IC1.19 (1Q), U$1.31 (A15)
unnamed: IC1.18 (2Q), U$1.2 (A16)
unnamed: IC1.17 (3Q), U$1.30 (A17)
unnamed: IC1.16 (4Q), U$1.1 (A18)
unnamed: U$1.29 (!WE), U$2.27 (_WE)
unnamed: U$1.22 (!CE), U$2.20 (_CS)
unnamed: U$1.24 (!OE), U$2.22 (_OE)
unnamed: D0.1, IC1.2 (1D)
unnamed: D1.1, IC1.3 (2D)
unnamed: D2.1, IC1.4 (3D)
unnamed: D3.1, IC1.5 (4D)
unnamed: GRAMBANKSEL.1, IC1.11 (C)
VCC: IC1.20 (VCC), U$1.32 (VDD), U$2.28 (VCC)

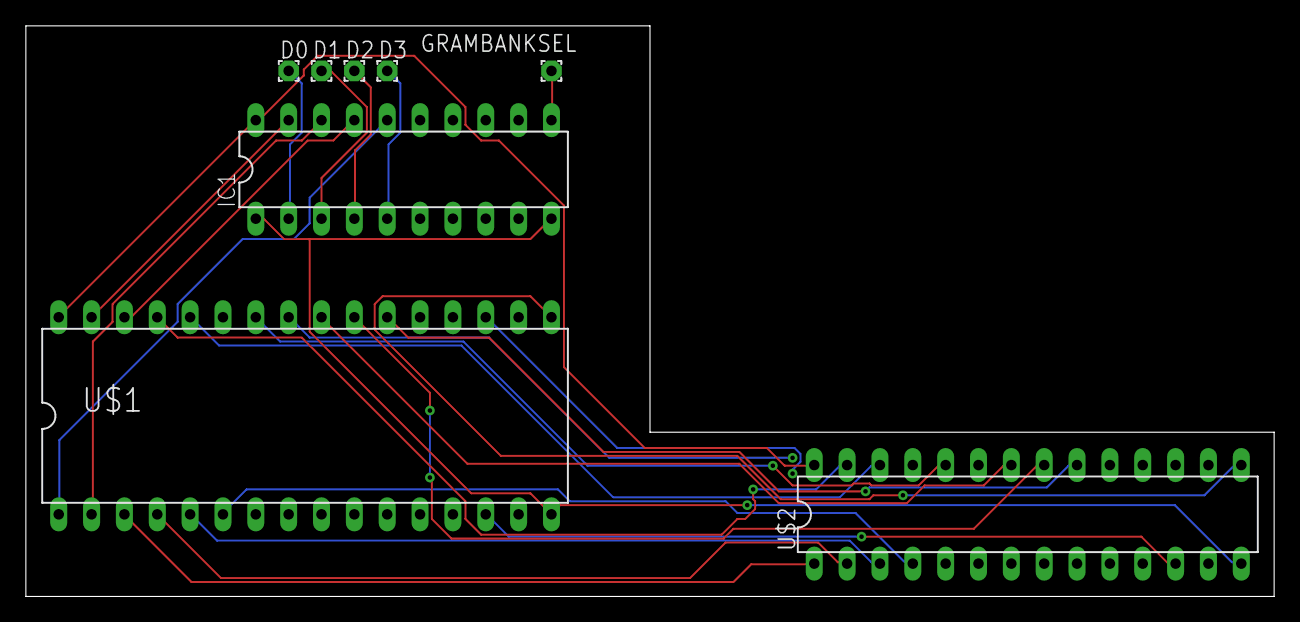
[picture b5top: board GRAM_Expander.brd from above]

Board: 4 copper layers, 96.5 x 44.1 mm, 8 parts (0 on the bottom side), 37 nets.

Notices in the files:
parts and their libraries:
SparkFun-Boards: Licensing: Creative Commons ShareAlike 4.0 International - https://creativecommons.org/licenses/by-sa/4.0
